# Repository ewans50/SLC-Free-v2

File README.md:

I'm not a creator of this product, please see https://www.14point7.com/pages/software-and-documentation for latest updates from the creator

SLC Free 2 is licensed under GNU GPL V3

Use Cypress PSOC Designer 5.4 to build/compile Firmware

Prebuilt hex files that are ready to program onto blank uCs using the PSOC Programmer Software and PSOC MiniProg hardware are contained in the "Firmware\Prebuilt_Hex" directory

PCB_Gerber_6mil_Trace_Spacing.rar in "PCB" directory are the Gerber files that you can submit to PCB fabrication places

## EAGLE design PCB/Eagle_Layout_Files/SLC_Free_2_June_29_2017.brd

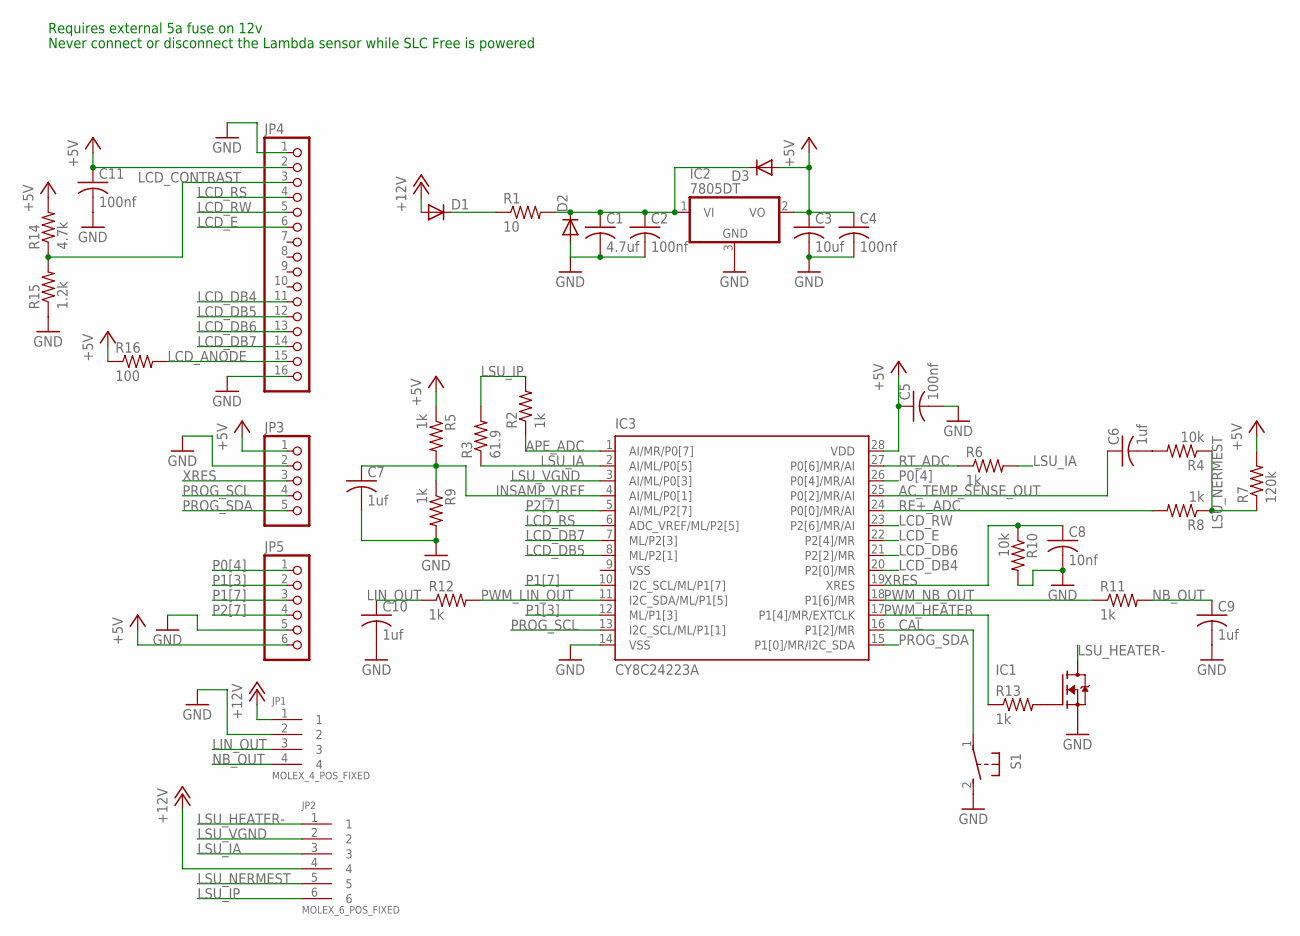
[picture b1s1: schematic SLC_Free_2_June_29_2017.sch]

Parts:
C1: 4.7uf; C1210
C2, C4, C5, C11: 100nf; C0805
C3: 10uf; C1206
C6, C7, C9, C10: 1uf; C0805
C8: 10nf; C0805
D1, D2: DIODE-SMB; SMB
D3: DIODE-SOD123; SOD123
IC1: FET_NMOS_T0252; T0252
IC2: 7805DT; TO252
IC3: CY8C24223A; SSOP28
JP1: MOLEX_4_POS_FIXED
JP2: MOLEX_6_POS_FIXED
JP3: PINHD-1X5; 1X05
JP4: PINHD-1X16; 1X16
JP5: PINHD-1X6; 1X06
R1: 10; R1206
R2, R5, R6, R8, R9, R11, R12, R13: 1k; R0805
R3: 61.9; R0805
R4, R10: 10k; R0805
R7: 120k; R0805
R14: 4.7k; R0805
R15: 1.2k; R0805
R16: 100; R1206
S1: 31-XX; B3F-31XX

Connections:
+5V: C3.1, C4.1, C5.1, C11.1, D3.A, IC2.2 (VO), IC3.28 (VDD), JP3.1, JP4.2, JP5.6, R5.1, R7.2, R14.2, R16.1
+12V: D1.A, JP1.1, JP2.4
AC_TEMP_SENSE_OUT: C6.1, IC3.25 (P0[2]/MR/AI)
APE_ADC: IC3.1 (AI/MR/P0[7]), R2.1
CAL: IC3.16 (P1[2]/MR), S1.1
GND: C1.2, C2.2, C3.2, C4.2, C5.2, C7.2, C8.2, C9.2, C10.2, C11.2, D2.A, IC1.2 (S), IC2.3 (GND), IC3.14 (VSS), JP1.2, JP3.2, JP4.1, JP4.16, JP5.5, R9.2, R10.2, R15.1, S1.2 (S)
INSAMP_VREF: C7.1, IC3.4 (AI/ML/P0[1]), R5.2, R9.1
LCD_ANODE: JP4.15, R16.2
LCD_CONTRAST: JP4.3, R14.1, R15.2
LCD_DB4: IC3.20 (P2[0]/MR), JP4.11
LCD_DB5: IC3.8 (ML/P2[1]), JP4.12
LCD_DB6: IC3.21 (P2[2]/MR), JP4.13
LCD_DB7: IC3.7 (ML/P2[3]), JP4.14
LCD_E: IC3.22 (P2[4]/MR), JP4.6
LCD_RS: IC3.6 (ADC_VREF/ML/P2[5]), JP4.4
LCD_RW: IC3.23 (P2[6]/MR/AI), JP4.5
LIN_OUT: C10.1, JP1.3, R12.1
LSU_HEATER-: IC1.3 (D), JP2.1
LSU_IA: IC3.2 (AI/ML/P0[5]), JP2.3, R3.1, R6.2
LSU_IP: JP2.6, R2.2, R3.2
LSU_NERMEST: JP2.5, R4.1, R7.1, R8.1
LSU_VGND: IC3.3 (AI/ML/P0[3]), JP2.2
unnamed: C6.2, R4.2
unnamed: C1.1, C2.1, D2.C, D3.C, IC2.1 (VI), R1.2
unnamed: IC1.1 (G), R13.2
unnamed: D1.C, R1.1
NB_OUT: C9.1, JP1.4, R11.2
P0[4]: IC3.26 (P0[4]/MR/AI), JP5.1
P1[3]: IC3.12 (ML/P1[3]), JP5.2
P1[7]: IC3.10 (I2C_SCL/ML/P1[7]), JP5.3
P2[7]: IC3.5 (AI/ML/P2[7]), JP5.4
PROG_SCL: IC3.13 (I2C_SCL/ML/P1[1]), JP3.4
PROG_SDA: IC3.15 (P1[0]/MR/I2C_SDA), JP3.5
PWM_HEATER: IC3.17 (P1[4]/MR/EXTCLK), R13.1
PWM_LIN_OUT: IC3.11 (I2C_SDA/ML/P1[5]), R12.2
PWM_NB_OUT: IC3.18 (P1[6]/MR), R11.1
RE+_ADC: IC3.24 (P0[0]/MR/AI), R8.2
RT_ADC: IC3.27 (P0[6]/MR/AI), R6.1
VSS: IC3.9 (VSS)
XRES: C8.1, IC3.19 (XRES), JP3.3, R10.1

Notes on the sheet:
Requires external 5a fuse on 12v
Never connect or disconnect the Lambda sensor while SLC Free is powered

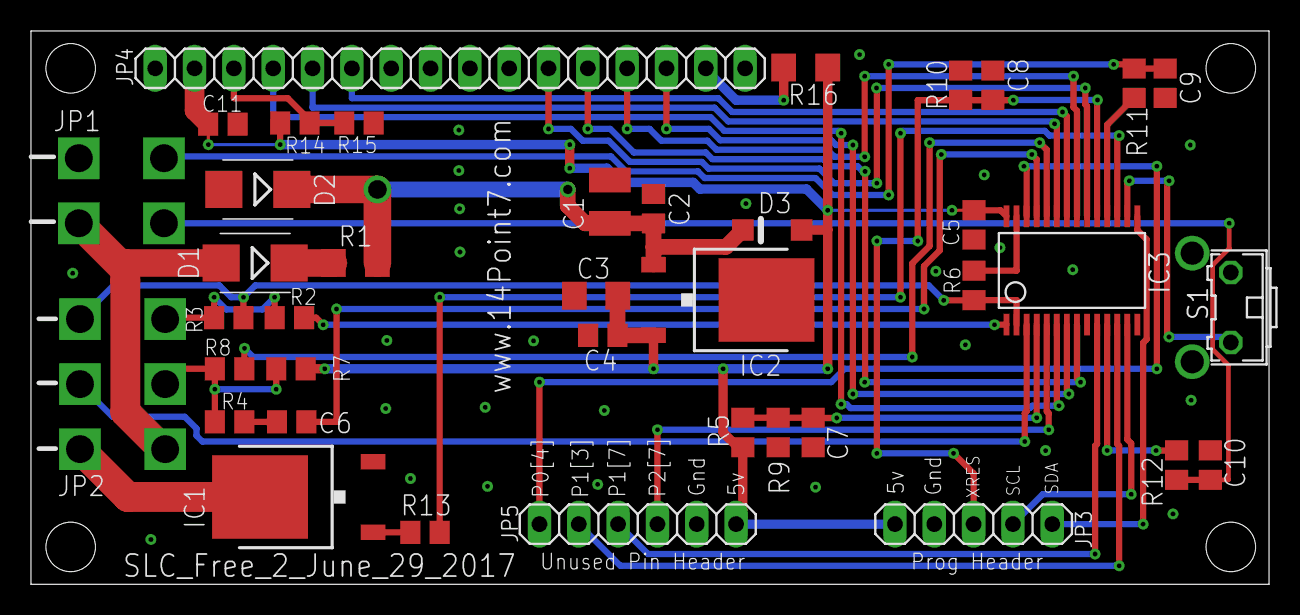
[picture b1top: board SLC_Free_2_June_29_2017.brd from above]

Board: 2 copper layers, 80.0 x 35.7 mm, 39 parts (0 on the bottom side), 39 nets.
